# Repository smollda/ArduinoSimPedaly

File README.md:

# ArduinoSimPedaly
Připojení 3 pedálů s použitím loadcellů a 3 modulů HX711

Pozor - pro úspěšné dokončení tohoto projektu je nutné znát základy arduina a celkově programování (po pár tutoriálech na netu podle mně zvládne každý). Zapojit se to dá i pomocí propojovacích kablíků pro nepájivá pole a menší svorkovnice, ale lepší je to připájet alespoň na univerzální plošný spoj - takže pájka, cín a nějaká zkušenost s nimi se taky hodí

V souborech je i můj návrh na plošný spoj tvořený v kicadu (Pedaly.zip) a soubor Pedaly.kicad_pcb, který stačí poslat například sem https://www.plosnaky.cz/ a nechat si ho vyrobit.

V aktuální verzi softwaru mám zakomentován spojkový pedál, protože ho zatím nemám hotový.

Použité knihovny:
HX711 multi https://github.com/compugician/HX711-multi
Arduino Joystick 2.0 https://github.com/MHeironimus/ArduinoJoystickLibrary

# Seznam materiálu:
Arduino Micro / Arduino Leonardo (např. https://www.gme.cz/100-kompatibilni-klon-arduino-micro-atmega32u4-5v)
(pro můj návrh plošného spoje je potřeba konkrétně typ Micro!)

HX711 modul (např. https://www.laskarduino.cz/ad-prevodnik-modul-24-bit-2-kanaly-hx711/)

3x loadcell

V případě osazení na plošný spoj navíc:

Svorkovnice (např. 4x https://www.gme.cz/svorkovnice-ptr-akz700-3-5-08-v-green)

Případně dutinkové lišty - arduino a HX711 moduly se pak nepájí přímo na PCB, ale nacvaknou se do těchto lišt (tohle řešení silně doporučuji!) https://www.gme.cz/dutinkova-lista-bl04g 4x, https://www.gme.cz/dutinkova-lista-bl806g 4x, https://www.gme.cz/dutinkova-lista-bl15g 2x (arduino nemá využity všechny piny, proto stačí 15 pinová dutinková lišta, nebo i kratší

# Zapojení:

Viz Schema.png. Na HX711 modulech je potřeba udělat úpravu pro běh na 80Hz (v základu běží na 10 Hz) - viz hx711_uprava.jpg. Svorkovnice označená jako příprava pro ručku je myšlena pro připojení případného čtvrtého HX711 modulu, umístěného v ruční brzdě - zatím jenom příprava do budoucna. Ve výsledku nejspíš ručku zapojím na separátní arduino třeba s button boxem.

# Program:
Soubor loadcellyHX711.ino obsahuje můj aktuální sketch, který použvám. V podstatě jde jenom o přečtení hodnot ze všech HX711 do pole results[], přepočet těchto hodnot do rozsahu pro knihovnu joystick (v mém sketchi je rozsah špatně, přícházím o přesnost. Správně by na výstup mělo jít číslo mezi -32767 a 32767).

Soubor Pedaly.ino obsahuje novější verzi, kde si arduino samo přepočítá hodnoty vyčtené z HX711 modulů do rozsahu -32767 / 32767. Při prvním spuštění je potřeba provést "kalibraci" - program přečte EEPROM pamět arduina, kde jsou uloženy minimální a maximální hodnoty všech pedálů. Pokud tam tyto hodnoty nejsou (po prvním nahrání tohoto sketche), spustí kalibraci - do konzole vypíše "Start kalibrace" (v tu chvíli je potřeba nechat pedály v základní poloze), dále "Minimální hodnoty: Pedál 1: x, pedál 2: y, pedál 3:z", kde x, y a z jsou hodnoty přečtené z HX711 modulů. Následně se do konzole vypíše "Sešlápni opakovaně všechny 3 pedály na doraz do 10 sekund (brzdu dle libosti)". V tu chvíli je potřeba během následujících 10 sekund sešlápnout všechny 3 pedály, klidně opakovaně. Program uloží maximální hodnoty všech pedálů a použije je pro přepočet hodnot pro výstup na jednotlivé osy (to je ten zmiňovaný rozsah -32767 / 32767). Hodnoty jsou uloženy do paměti EEPROM arduina, zůstanou tedy zachované i po restartu / vypnutí napájení. V některých případech i při přehrání softwaru arduina, tam záleží jak je nastaven bootloader. 

"Kalibraci" pedálů lze znovu provést otevřením konzole v arduino IDE (nástroje -> Seriový monitor) a odesláním znaku "k" (stiskem tlačítka "pošli").

Změna 20.7.2020 - program Pedaly.ino upraven tak, aby neaktualizoval pozici pedálu, pokud přečte z HX711 modulu nesmyslnou hodnotu (extrémně vysoká kladná/záporná hodnota). Použitá knihovna nemá ošetřeno, zda je hodnota přečtená z HX711 modulu platná a jednou za x sekund se stane, že přečte nesmysl - zatím nevím čím je to způsobeno. 
Pokud by náhodou k chybě došlo i během kalibrace, nebude mít pedál správný rozsah - v tom případě stačí kalibraci provést znovu.

Konečnou kalibraci pedálů ve windows (deadzony atd.) lze provést programem DIview stejně jako u Heusinkveld pedálů - viz návod https://www.youtube.com/watch?v=b3Ut4R1O-Sw.

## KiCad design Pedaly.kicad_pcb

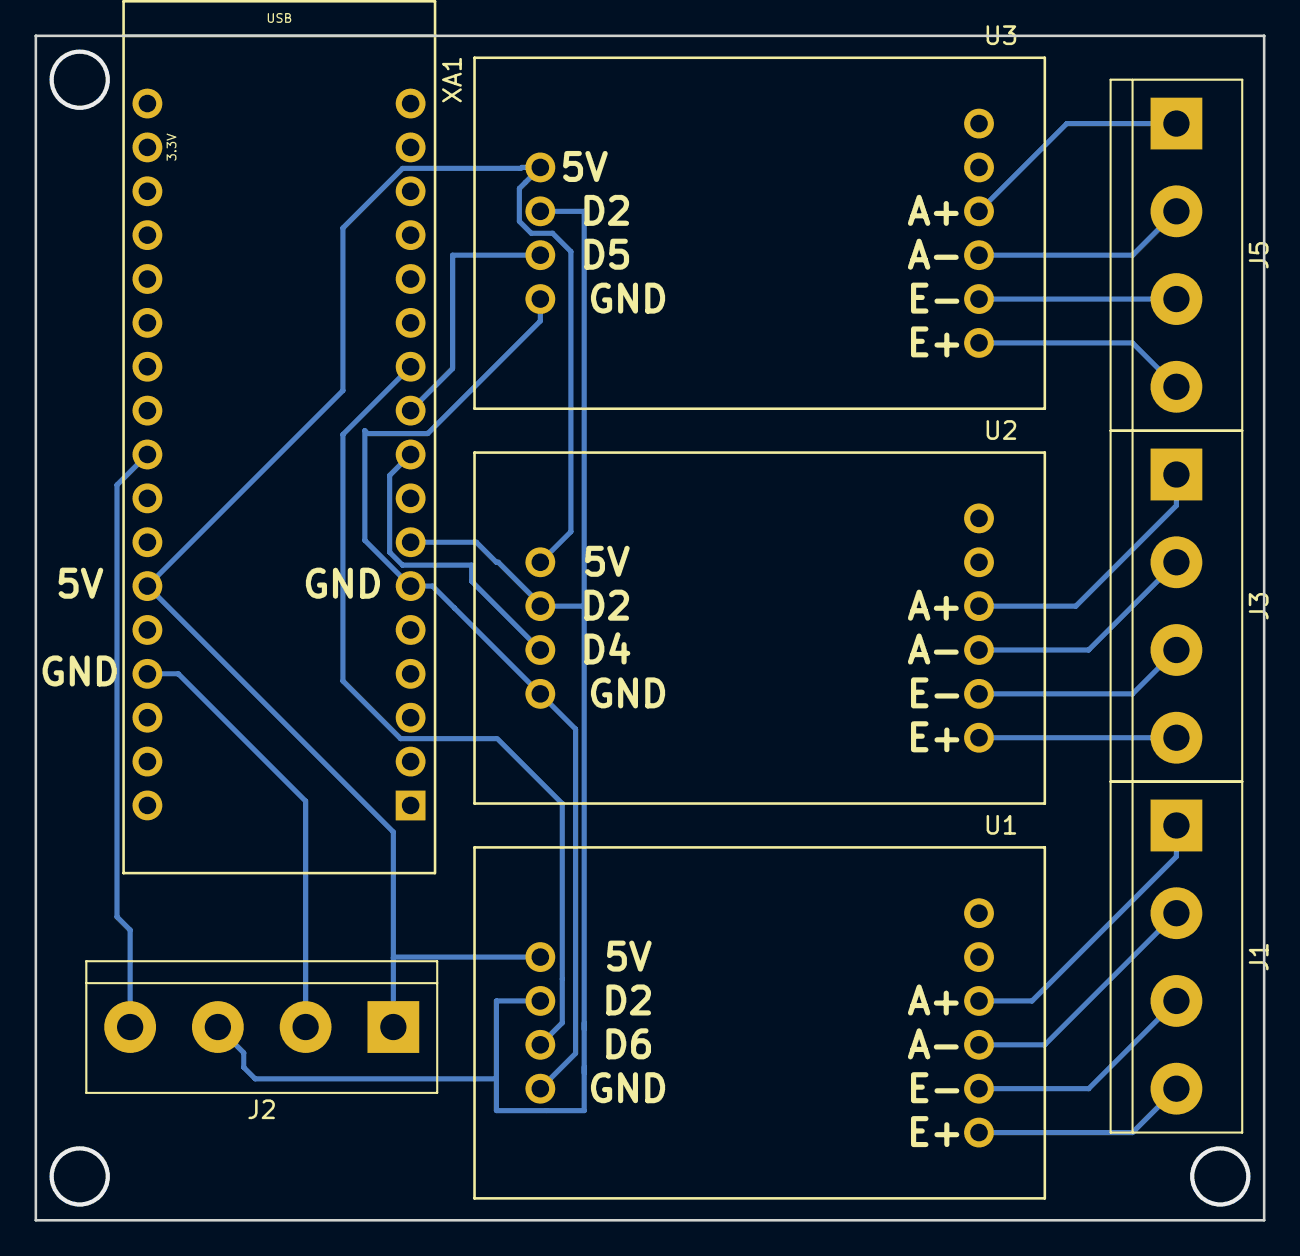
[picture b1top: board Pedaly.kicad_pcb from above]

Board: 2 copper layers, 71.1 x 68.6 mm, 8 parts (0 on the bottom side), 19 nets.

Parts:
J1, J3, J5: Screw_Terminal_01x04; TerminalBlock_bornier-4_P5.08mm
J2: Ručka - příprava; TerminalBlock_bornier-4_P5.08mm
U1, U2, U3: HX711
XA1: Arduino_Micro; Arduino_Micro_Socket_uprava

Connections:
unnamed: J1.1, U1.4
unnamed: J1.2, U1.3
unnamed: J1.3, U1.2
unnamed: J1.4, U1.1
unnamed: J2.1, U1.10, U2.10, U3.10, XA1.5V
unnamed: J2.2, U1.7, U2.7, U3.7, XA1.GND1, XA1.GND2
unnamed: J2.3, U1.9, U2.9, U3.9, XA1.D2
unnamed: J2.4, XA1.A5
unnamed: J3.1, U2.4
unnamed: J3.2, U2.3
unnamed: J3.3, U2.2
unnamed: J3.4, U2.1
unnamed: J5.1, U3.4
unnamed: J5.2, U3.3
unnamed: J5.3, U3.2
unnamed: J5.4, U3.1
unnamed: U1.8, XA1.D6
unnamed: U2.8, XA1.D4
unnamed: U3.8, XA1.D5

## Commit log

2021-03-06 Update pedaly.ino
    V definici typu joysticku odstraněna tlačítka
